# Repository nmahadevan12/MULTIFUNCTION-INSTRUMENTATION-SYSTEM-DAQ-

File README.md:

# Multifunction Instrumentation System (M.I.S.)

**Developed by Nikhil Mahadevan**

A portable, Raspberry Pi–powered electronic test bench that replaces six lab instruments — ohmmeter, voltmeter, DC reference, square/sine function generator, and frequency meter — with one integrated DAQ platform.

---

## Table of Contents

- [Overview](#overview)
- [Instrument Summary](#instrument-summary)
- [System Architecture](#system-architecture)
- [Software Architecture](#software-architecture)
- [Hardware Design](#hardware-design)
  - [Power Supply](#41--12-v-power-supply)
  - [Ohmmeter](#42-ohmmeter)
  - [Voltmeter](#43-voltmeter)
  - [DC Reference](#44-dc-reference)
  - [Square Wave Generator](#45-square-wave-generator)
  - [Sine Wave Measurement](#46-sine-wave-measurement-frequency-meter)
  - [Sine Wave Generator](#47-sine-wave-generator)
- [PCB Design](#pcb-design-kicad)
- [GPIO Pin Map](#gpio-pin-map-system)
- [Getting Started](#getting-started)
- [Demo Videos](#demo-videos)
- [Skills Demonstrated](#skills-demonstrated)

---

## Overview

The Multifunction Instrumentation System integrates oscilloscopes, function generators, and multimeters into a single-board computer platform using the **Raspberry Pi 4** as the central processing unit. Custom analog front-end circuits handle signal conditioning, comparison, and generation; Python firmware orchestrates measurement, waveform output, and a responsive menu-driven UI from a single application.

> [!TIP]
> **Documentation convention:** Images show only schematics, photos, and oscilloscope captures. All objectives, theory, and figure captions are written as markdown text below each image.

<details open>
<summary><strong>At a Glance</strong></summary>

| | |
|---|---|
| **Controller** | Raspberry Pi 4 (sole processor — no external MCU) |
| **Interface** | 20×4 I²C LCD + KY-040 rotary encoder with pushbutton |
| **Analog front-end** | TL084/TL081 op-amps, LM339 comparators, MCP4131/MCP4231 digipots |
| **Power** | 24 V DC input → ±12 V virtual-ground split-rail supply |
| **Firmware** | ~970 lines of Python — SAR measurement, hardware PWM, pigpio edge detection |
| **PCB** | 4-layer KiCad hierarchical design with Gerber manufacturing files |

</details>

<details>
<summary><strong>Project Objectives</strong></summary>

1. **Instrument design**
   - Ohmmeter (500 Ω – 10 kΩ)
   - Voltmeter (−5 V to +5 V)
   - DC reference (−5 V to +5 V)
   - Sine wave frequency measurement (1 – 10 kHz)
   - Function generator — square wave (100 Hz – 10 kHz, ±10 V) and sine wave (1 – 10 kHz, 0 – 10 V pk)

2. **System integration**
   - ±12 V power supply from 24 V input
   - Software-driven successive-approximation measurement (digipot + comparator)
   - Rotary-encoder UI on 20×4 LCD

3. **PCB layout**
   - Full KiCad schematic and 4-layer board design sized to the Raspberry Pi footprint

</details>

<details>
<summary><strong>Design Constraints</strong></summary>

| Category | Constraint |
|---|---|
| **Software** | All logic in Python; pigpio daemon for timing-critical PWM and edge detection |
| **Controller** | Raspberry Pi 4 only — no external microcontrollers |
| **Digipots** | Maximum of 4 digital potentiometers (MCP4131 ×3, MCP4231 ×1 dual-channel) |
| **Power** | All analog power derived from 24 V DC (LCD powered separately); Pi via USB-C |
| **Mechanical** | Pi Hat required — all GPIO routed through hat connector |

</details>

---

## Instrument Summary

| Instrument | Range | Accuracy | Update Rate |
|:---|:---|:---|:---|
| 🔵 **Ohmmeter** | 500 Ω – 10 kΩ | ±10% | 500 ms |
| 🟢 **Voltmeter** | −5 V to +5 V | ±0.2 V | 500 ms |
| 🟡 **DC Reference** | −5.00 V to +4.80 V (32 steps) | ±0.2 V | On demand |
| 🟠 **Square Wave** | 100 Hz – 10 kHz, ±10 V pk | ±1 V amplitude | Real-time PWM |
| 🟣 **Sine Wave** | 1 – 10 kHz, 0 – 10 V pk | ±0.2 V amplitude | Real-time audio |
| 🔴 **Frequency Meter** | 1 – 10 kHz | ±1% | 500 ms |

---

## System Architecture

```mermaid
flowchart LR
    subgraph UI["🖥️ User Interface"]
        LCD["20×4 I²C LCD"]
        ENC["Rotary Encoder"]
    end

    subgraph SW["🐍 Python Firmware"]
        MENU["Menu State Machine"]
        SAR["SAR Engine"]
        PWM["Hardware PWM"]
        FREQ["Edge Detection"]
    end

    subgraph HW["⚡ Analog Front-End"]
        PS["±12V Supply"]
        MEAS["Ohm / Volt"]
        GEN["Wave Gen"]
        DCREF["DC Ref"]
    end

    ENC --> MENU --> LCD
    MENU --> SAR & PWM & FREQ
    SAR & PWM & FREQ --> HW
    PS --> HW
```

---

## Software Architecture

Software is the core of the system — it links the user interface to hardware modules, converts raw comparator signals into resistance/voltage values, controls waveform timing, and keeps the LCD updated.

<details open>
<summary><strong>Platform & Libraries</strong></summary>

| Layer | Technology |
|---|---|
| OS | Raspberry Pi OS |
| Execution | Standalone Python script (`Main Code/16.py`) |
| GPIO / PWM | `RPi.GPIO`, `pigpio` (hardware PWM + µs edge timestamps) |
| SPI | `spidev` — MCP4131 / MCP4231 digital potentiometers |
| I²C | `smbus2`, `RPLCD` — 20×4 character LCD |
| UI input | `gpiozero` — rotary encoder + button callbacks |

</details>

<details>
<summary><strong>Navigation & Main Loop</strong></summary>

The interface is a **stack-based menu tree** with automatic hardware cleanup on back-navigation. Measurement modes sample every **500 ms**; the LCD refreshes on a 50 ms display flag with thread-safe writes.

To ensure a highly responsive user interface, the **500 ms** hardware measurement routines run asynchronously or utilize non-blocking sleep intervals. This prevents the synchronous 8-bit SPI SAR sweeps from blocking encoder interrupt callbacks or delaying the **50 ms** LCD UI refresh cycle.

```
while True:
    if display_needs_update → render_interface()
    if measurement_mode     → sample hardware every 500 ms
    if leaving_mode         → cleanup GPIO / stop waveforms
    sleep(0.05)
```

</details>

<details>
<summary><strong>Per-Instrument Firmware</strong></summary>

| Instrument | Key Implementation |
|---|---|
| **Square wave** | Hardware PWM GPIO 12 + MCP4231 amplitude/offset over SPI |
| **Sine wave** | Pi audio jack + `speaker-test`; MCP4131 amplitude (CS GPIO 17) |
| **Ohmmeter** | 8-iter SAR on MCP4131; `R = R_known × (step / (128 − step))` |
| **Voltmeter** | SAR on GPIO 6; lookup table + linear interpolation |
| **DC Reference** | 5-bit R-2R on GPIO 14, 15, 18, 23, 24 |
| **Frequency** | pigpio edge callbacks GPIO 25; 100-period buffer, >2σ outlier reject |

</details>

> [!IMPORTANT]
> All waveform and DC outputs **automatically disable** when leaving a menu — a built-in safety interlock.

---

## Hardware Design

### 4.1 ±12 V Power Supply

*Figure 4.1.1: Power Supply Schematic*

<details open>
<summary><strong>Power Supply — Theory & Integration</strong></summary>

**Objective:** Split a +24 V DC input into symmetric +12 V and −12 V rails to power op-amps throughout the system. Rails must remain stable under varying load.

**Theory of Operation:** Virtual ground from a 24 V source. TL081 unity-gain follower at the 12 V midpoint drives IRFZ34N + IRF5305 push-pull stage. Virtual ground tied to Pi GND → +12 V above, −12 V below. The virtual ground node acts as the absolute **0 V** reference point for all analog measurements. To prevent heavy analog return currents from injecting noise into the digital plane, the Raspberry Pi GND is tied to this virtual ground at a **single star-ground point** right at the power entry terminal.

1. **Voltage reference:** Matched 10 kΩ divider + Zener clamping → 12 V at TL081 pin 3
2. **Unity-gain buffering:** 100 kΩ feedback drives MOSFET gates
3. **Push-pull output:** NMOS sources / PMOS sinks load current at virtual ground
4. **Output stabilization:** 220 µF bulk caps per rail

**Physical Integration:** Breadboard; ±12 V via terminal blocks. **GPIO:** None — analog only.

</details>

<details>
<summary><strong>Power Supply — Test Results</strong></summary>

| Test Condition | Negative Rail | Positive Rail | Current |
|---|---|---|---|
| Both loads connected | −12.04 V | +12.05 V | ~12 mA each |
| No load | −12.05 V | +12.06 V | — |
| Negative load only | 12.05 V | — | 12.10 mA |
| Positive load only | — | 12.06 V | 12.08 mA |

</details>

> [!WARNING]
> MOSFETs run warm under heavy load. Observe electrolytic capacitor polarity on each rail.

---

### 4.2 Ohmmeter

*Figure 4.2.1: Ohmmeter Schematic*

<details open>
<summary><strong>Ohmmeter — Theory & GPIO</strong></summary>

**Objective:** High-accuracy auto-ranging digital ohmmeter for **500 Ω to 10 kΩ**.

**Theory of Operation:** Voltage divider with unknown resistor vs. **7-bit MCP4131** programmable reference. Successive approximation across 128 wiper steps; LM339 comparator on GPIO 21. LCD updates every 500 ms with ±10% tolerance. A fixed series current-limiting resistor (**R_limit = 1 kΩ**) is placed in series with the unknown device under test (DUT). This keeps the maximum current through the MCP4131 wiper well below its absolute maximum rating of **2.5 mA** even when measuring low resistances down to **500 Ω**.

| Signal | GPIO | Component Pin |
|---|---|---|
| Chip Select (CS) | 8 | MCP4131 Pin 1 |
| SPI Clock (SCK) | 11 | MCP4131 Pin 2 |
| SPI Data (SDI/SDO) | 10 | MCP4131 Pin 3 |
| Comparator Output | 21 | LM339 Output |

> [!NOTE]
> **SAR performance (8-bit search):** Each iteration writes one MCP4131 wiper step over SPI (1 MHz, 2-byte frame ≈ 16 µs), waits **5 ms** for the divider/comparator to settle (`sleep(0.005)`), then reads GPIO 21. Eight bisection steps → **≈40 ms** per resistance reading, well under the **500 ms** LCD refresh cadence. Quantization is set by the **128-step** digipot (7-bit effective range); resistance resolution is non-linear with step (`R = R_known × step / (128 − step)`) and tightest near the matched mid-scale point. Because the voltage-divider topology yields a non-linear resolution across the 128-step digipot, measurement precision peaks when the unknown resistance closely matches the internal reference (**R_known**). Near the outer bounds (**500 Ω** and **10 kΩ**), step-size quantization broadens, which accounts for the specified worst-case **±10%** tolerance.

</details>

---

### 4.3 Voltmeter

*Figure 4.3.1: Voltmeter Schematic*

<details open>
<summary><strong>Voltmeter — Theory & GPIO</strong></summary>

**Objective:** Measure **−5 V to +5 V** at ±0.2 V accuracy. Dual-source: external input or internal DC reference verification.

**Theory of Operation:**

1. **U2 — Inverting summing amp:** Maps −5 V to +5 V → 0 V to −10 V
2. **U1 — Inverting amp:** Gain −1/3 → **0 to +3.3 V**
3. **U3 — MCP4131:** 128-step programmable reference via SPI
4. **U5A — LM339:** Comparator with 10 kΩ pull-up
5. **GPIO 6:** Binary search until reference matches test voltage

| Signal | GPIO | Component Pin |
|---|---|---|
| Chip Select (CS) | 8 | MCP4131 Pin 1 |
| SPI Clock (SCK) | 11 | MCP4131 Pin 2 |
| SPI Data (SDI/SDO) | 10 | MCP4131 Pin 3 |
| Comparator Output | 6 | LM339 Pin 13 |

> [!NOTE]
> **SAR performance (8-bit search):** Same 8-iteration binary search as the ohmmeter — one SPI wiper write + **5 ms** settle per step → **≈40 ms** total sweep, safely below the **500 ms** display refresh rate. The ±10 V input span maps to 128 comparator steps, giving a theoretical **≈78 mV/step** (`10 V / 128 ≈ 78 mV`); linear interpolation between calibrated lookup points improves display accuracy to ±0.2 V.

**Calibration & Testing:** Verified against reference multimeter across full range. SAR converges in 8 iterations. ±0.2 V accuracy; best precision near 0 V.

</details>

---

### 4.4 DC Reference

*Figure 4.4.1: DC Ref Schematic*

<details open>
<summary><strong>DC Reference — Theory</strong></summary>

**Objective:** Programmable DC output **−5 V to +5 V** in 0.625 V steps (32 levels).

1. **R-2R DAC:** GPIO 14, 15, 18, 23, 24 → binary-weighted divider
2. **U2 — Non-inverting amp:** Gain ≈ 3.03 scales 0–3.3 V → 0–10 V
3. **U3 — Difference amp:** +5 V bias → **−5 V to +5 V** output

**Calibration & Testing:** Output verified across all 32 steps with a reference multimeter. Monotonic response confirmed from −5 V to +5 V.

</details>

<details>
<summary><strong>Previous Design Iteration (Figure 4.4.2)</strong></summary>

*Figure 4.4.2: Previous DC Ref Schematic*

Original binary-weighted DAC with per-GPIO comparator buffers suffered **cross-loading**. R-2R ladder maintains uniform 2R impedance regardless of bit pattern. The R-2R ladder ensures the digital pins always see a constant output impedance of **R** (or **2R** depending on the node), preventing the voltage sag and non-monotonicity caused by varying pin source impedances in the previous binary-weighted layout.

</details>

---

### 4.5 Square Wave Generator

*Figure 4.5.1: Square Wave Schematic*

<details open>
<summary><strong>Square Wave — Theory & GPIO</strong></summary>

**Objective:** Variable square wave centered at **0 V**, up to **±10 V**, high-Z output for oscilloscope use.

**Theory:** Pi hardware PWM GPIO 12 → MCP4231 amplitude + offset → difference amplifier (gain 10) → ±10 V. The hardware PWM output from GPIO 12 passes through a dedicated **RC low-pass filter** stage to smooth high-frequency switching transients and stabilize the signal envelope before amplitude scaling, maintaining waveform integrity across the **100 Hz to 10 kHz** band.

| Signal | GPIO | MCP4231 Pin |
|---|---|---|
| PWM Output | 12 | Ch1 Pin B |
| Chip Select | 7 | Pin 1 |
| SPI Clock | 11 | Pin 3 |
| SPI Data In | 10 | Pin 4 |

**Calibration & Testing:**

- **Figure 4.5.2 — ±7 V initial:** −7.24 V min / +5.95 V max (miscentered)
- **Figure 4.5.3 — ±5 V @ 100 Hz:** Offset ratio **0.45** → ±3% centering
- **Figure 4.5.4 — ±10 V @ 100 Hz:** Full swing confirmed

</details>

<details>
<summary><strong>Oscilloscope Captures</strong></summary>

</details>

---

### 4.6 Sine Wave Measurement (Frequency Meter)

*Figure 4.6.1: Sine Wave Measurement Schematic*

<details open>
<summary><strong>Frequency Meter — Theory & GPIO</strong></summary>

**Objective:** Measure **0 V to +10 V** sine input frequency from **1 kHz to 10 kHz**.

**Theory:** LM339 threshold at **+1.65 V** → digital edges on GPIO 25 → **f = 1/T**. 100-period rolling buffer with >2σ outlier rejection.

**pigpio edge architecture:** On standard Linux (non-real-time), Python thread scheduling would jitter any bit-banged timing. The `pigpio` daemon sidesteps this by sampling GPIO transitions with **hardware-level DMA**, stamping each rising edge with a **microsecond-accurate tick** (`pigpio.tickDiff`) in a background buffer. The Python callback only appends period samples; `compute_frequency()` runs on the 500 ms UI loop, decoupling the timing-critical edge capture from GIL contention and kernel scheduling delay.

| Signal | GPIO | Component Pin |
|---|---|---|
| Comparator Output | 25 | LM339 Output |
| External Input | — | LM339 Non-Inverting Input |
| Reference (+1.65 V) | — | LM339 Inverting Input |

**Calibration & Testing:** ±2% tolerance across 1 – 10 kHz.

</details>

---

### 4.7 Sine Wave Generator

<details open>
<summary><strong>Sine Wave Generator — Theory & GPIO</strong></summary>

**Objective:** **0 – 10 V peak** sine wave from **1 kHz to 10 kHz**.

1. **U3 — TL081 buffer:** Pi audio jack + −5 V DC offset
2. **U4 & U5 — Scaling:** Normalize to 0–3.3 V. Because the Raspberry Pi audio jack outputs a line-level AC signal (≈1 V pk-pk), **U4** is configured as a non-inverting amplifier with a hardware gain of **A_v ≈ 3.3** to scale the raw audio voltage up to the required **3.3 V** internal logic dynamic range before attenuation.
3. **U10 — MCP4131:** Digital attenuation via SPI
4. **U11 & U12 — Output:** Reconstruct to 0–10 V

| Signal | GPIO | MCP4131 Pin |
|---|---|---|
| Chip Select | 17 | Pin 1 |
| SPI Clock | 11 | Pin 2 |
| SPI Data | 10 | Pin 3 |

</details>

---

## PCB Design (KiCad)

*Figure 5.2.1: Final PCB Schematic*

*Figure 5.2.2: Final PCB Board*

<details>
<summary><strong>PCB Design Details</strong></summary>

- **CAD tool:** KiCad — free, full-featured
- **Schematic:** Hierarchical sub-sheets per instrument; max 4 layers
- **Layout:** Subsystem grouping, through-hole + SMD passives, 45° routing
- **Manufacturing:** DRC-checked Gerbers in `PCBDesign/` (designed, not manufactured)

</details>

---

## GPIO Pin Map (System)

<details open>
<summary><strong>Full GPIO Map — click to expand</strong></summary>

| GPIO | Signal | Component | Description |
|:---:|:---|:---|:---|
| 2, 3 | SDA, SCL | LCD | I²C character display |
| 6 | Input | LM339 | Voltmeter comparator |
| 7 | SPI CS | MCP4231 | Square wave digipot |
| 8 | SPI CS | MCP4131 | Ohmmeter / voltmeter digipot |
| 10 | SPI MOSI | MCP4131/4231 | SPI data |
| 11 | SPI SCLK | MCP4131/4231 | SPI clock |
| 12 | HW PWM | — | Square wave output |
| 13, 19 | Input | KY-040 | Rotary encoder A/B |
| 14, 15, 18, 23, 24 | Output | R-2R ladder | DC reference (5-bit) |
| 17 | SPI CS | MCP4131 | Sine amplitude digipot |
| 21 | Input | LM339 | Ohmmeter comparator |
| 25 | Interrupt | LM339 | Frequency measurement |
| 26 | Input | KY-040 | Encoder button (3 s hold = back) |

</details>

---

## Getting Started

> [!NOTE]
> GPIO access requires `sudo`. The `pigpio` daemon must be running for PWM and frequency measurement.

<details open>
<summary><strong>Install & Run</strong></summary>

```bash
sudo apt update && sudo apt install -y python3-pip pigpio python3-pigpio alsa-utils
sudo systemctl enable --now pigpio
pip install -r requirements.txt
sudo python3 "Main Code/16.py"
```

</details>

<details>
<summary><strong>Controls Cheat Sheet</strong></summary>

| Action | Control |
|---|---|
| Scroll | Rotate encoder |
| Select / confirm | Short press |
| Back / cancel | Hold 3 seconds |
| Edit value | Rotate in edit mode, press to confirm |

Power Pi via **USB-C**, analog circuits via **24 V DC**. Wait ~20 s after boot.

</details>

---

## Demo Videos

<details open>
<summary><strong>Watch demos — click any link</strong></summary>

| Feature | Link |
|---|---|
| Power-on & setup | [YouTube](https://youtu.be/CEZYySeiEv4) |
| Menu navigation | [YouTube](https://youtu.be/Nd_8IkFf7bE) |
| Ohmmeter | [YouTube](https://youtu.be/j0UAiwsbkE0) |
| Voltmeter (external) | [YouTube](https://youtube.com/shorts/AqCL2ivuH78) |
| Voltmeter (internal ref) | [YouTube](https://youtube.com/shorts/lTq6MlFrF2s) |
| Square wave | [YouTube](https://youtube.com/shorts/NfCk3m-b2u8) |
| Sine wave | [YouTube](https://youtube.com/shorts/mf1v4rBYL3M) |
| Frequency measurement | [YouTube](https://youtube.com/shorts/Z5qWBG-sBkY) |

</details>

---

## Future Improvements

> [!TIP]
> Planned next steps: 12–16 bit external ADC, manufactured 4-layer PCB with ground planes, BNC/screw-terminal I/O, on-board regulators, active analog shielding.

---

## Skills Demonstrated

<table>
<tr>
<td width="50%">

**Embedded Systems**
- GPIO, hardware PWM, SPI/I²C
- pigpio edge detection
- SAR algorithms
- Thread-safe concurrent access

**Software Engineering**
- State-machine UI
- Stack navigation
- Lookup tables
- ~970 LOC firmware

</td>
<td width="50%">

**Analog Design**
- Op-amp conditioning
- Comparator front-ends
- R-2R DAC
- Virtual-ground power

**PCB / Systems**
- KiCad hierarchical design
- 4-layer layout
- End-to-end HW/SW co-design
- Safety interlocks

</td>
</tr>
</table>

---

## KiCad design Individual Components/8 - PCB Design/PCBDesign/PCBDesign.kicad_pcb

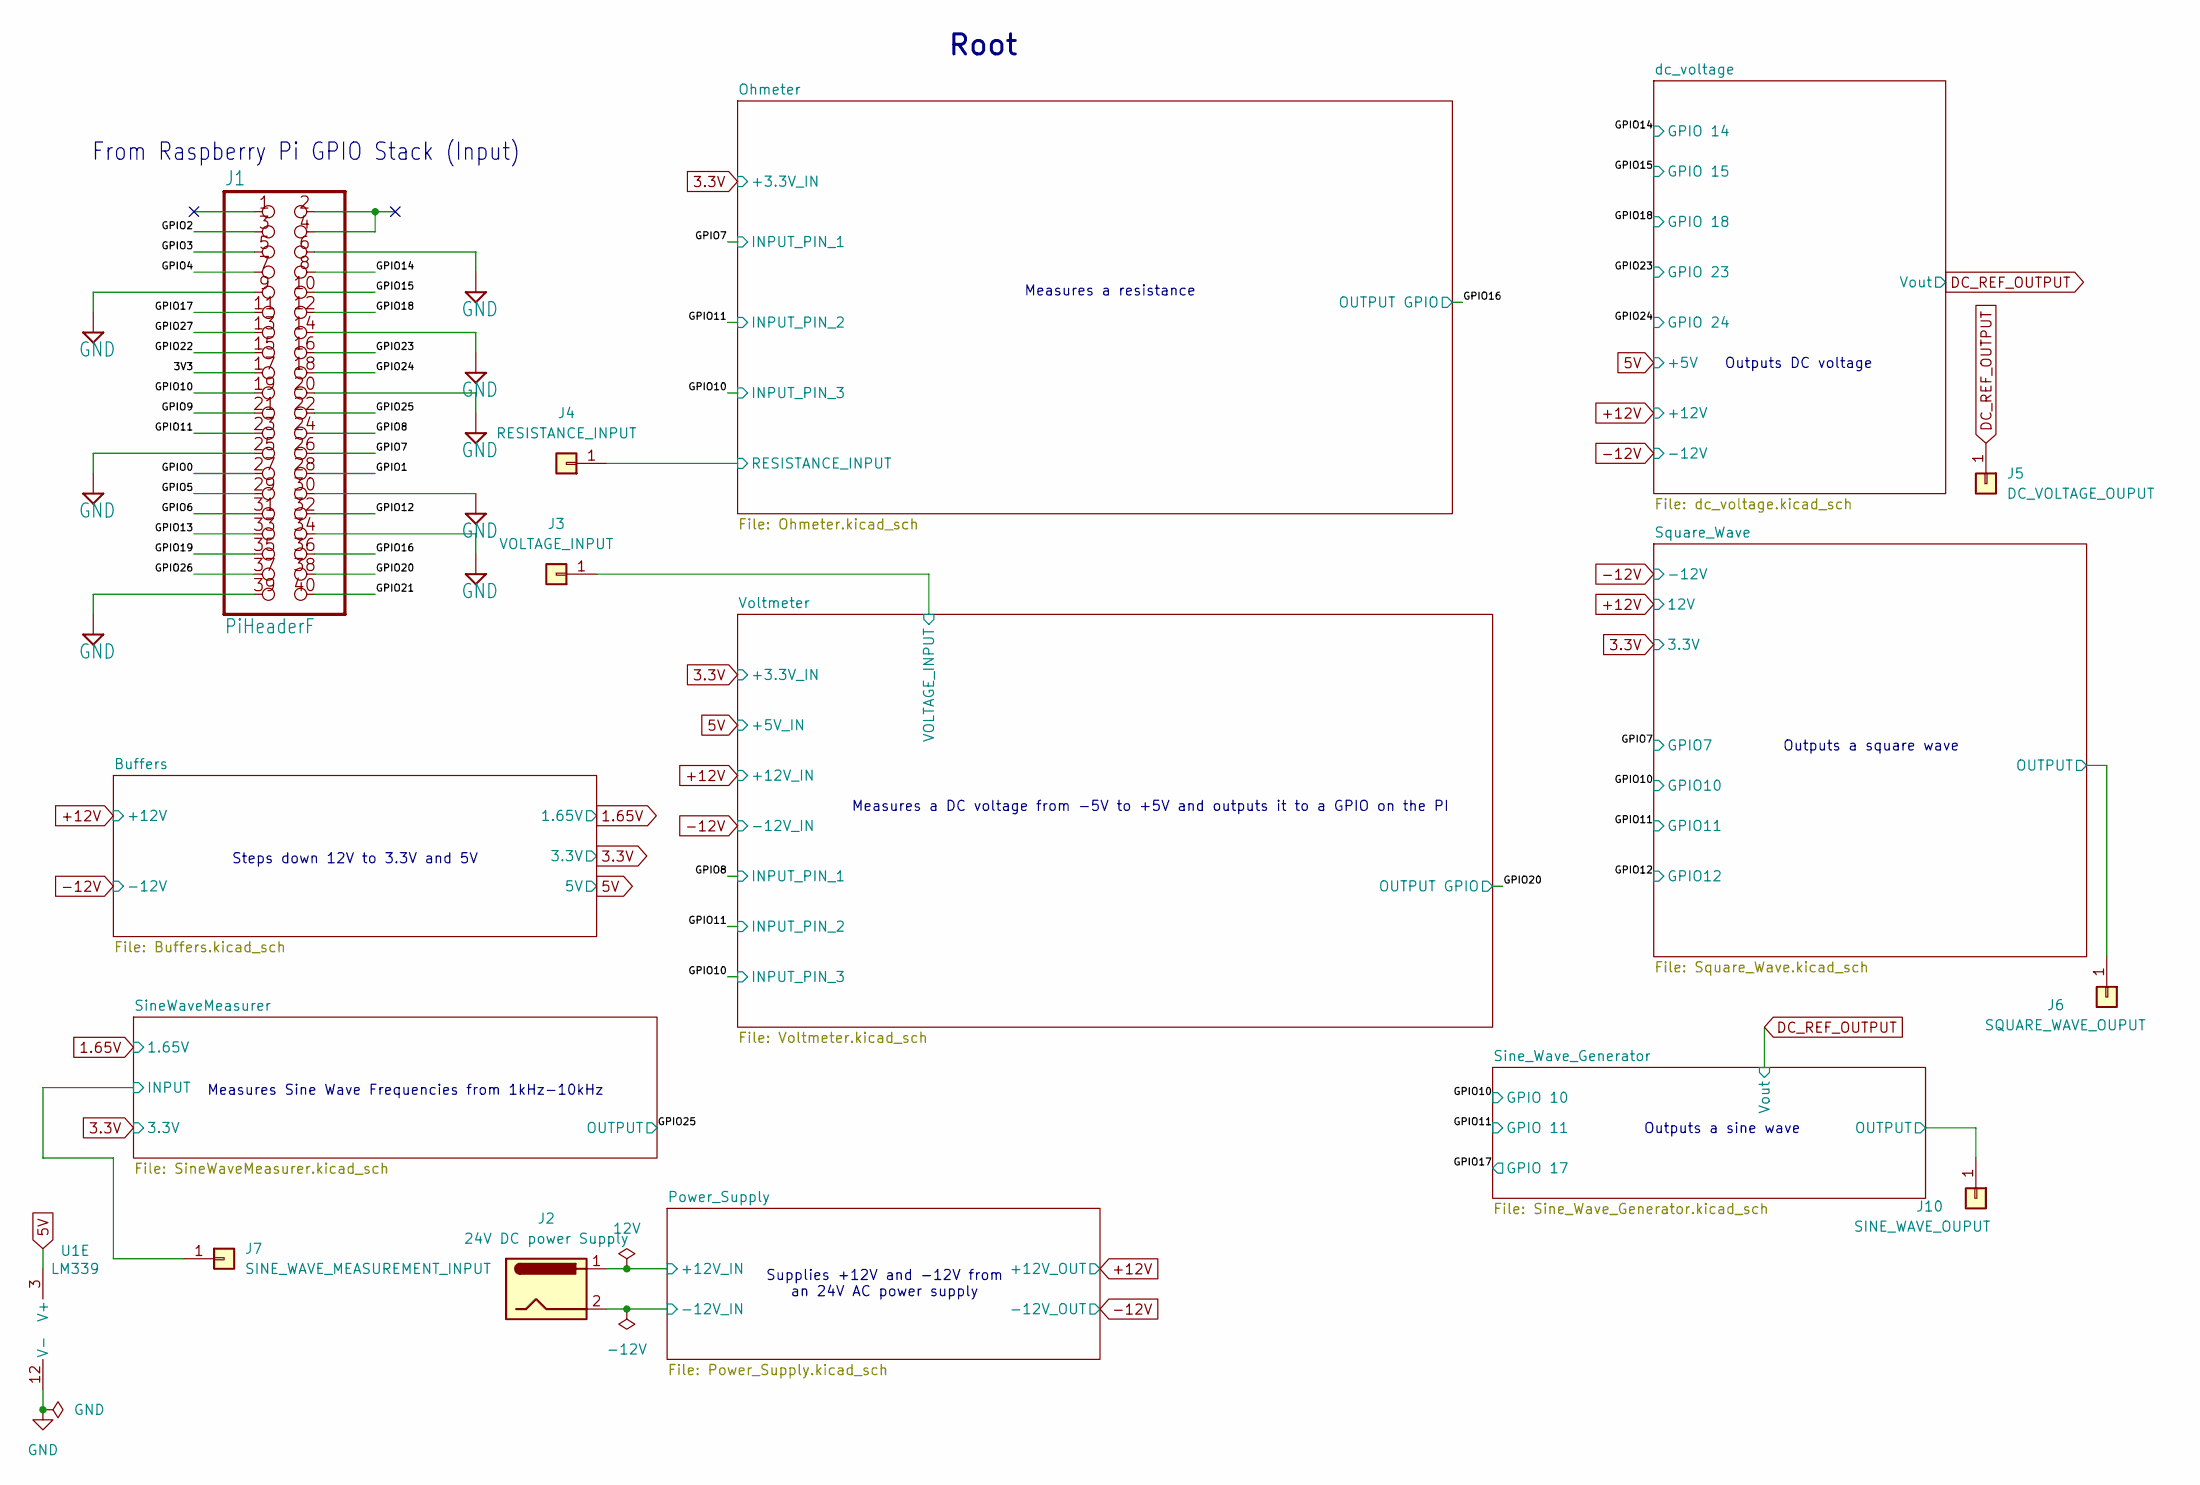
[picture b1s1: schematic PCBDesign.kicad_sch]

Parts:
J1: PiHeaderF; PinSocket_2x20_P2.54mm_Vertical
J2: 24V DC power Supply; BarrelJack_Horizontal
J3: VOLTAGE_INPUT; PinHeader_1x01_P1.00mm_Vertical
J4: RESISTANCE_INPUT; PinHeader_1x01_P1.00mm_Vertical
J5: DC_VOLTAGE_OUPUT; PinHeader_1x01_P1.00mm_Vertical
J6: SQUARE_WAVE_OUPUT; PinHeader_1x01_P1.00mm_Vertical
J7: SINE_WAVE_MEASUREMENT_INPUT; PinHeader_1x01_P1.00mm_Vertical
J10: SINE_WAVE_OUPUT; PinHeader_1x01_P1.00mm_Vertical
U1: LM339; DIP-14_W7.62mm

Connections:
3.3V: J4.1 (Pin_1_1); also elsewhere on the board
5V: U1.3 (V+); also elsewhere on the board
+12V: J2.1; also elsewhere on the board
-12V: J2.2; also elsewhere on the board
/3V3: J1.17
/GPIO0: J1.27
/GPIO1: J1.28
/GPIO2: J1.3
/GPIO3: J1.5
/GPIO4: J1.7
/GPIO5: J1.29
/GPIO6: J1.31
/GPIO7: J1.26; also elsewhere on the board
/GPIO8: J1.24; also elsewhere on the board
/GPIO9: J1.21
/GPIO10: J1.19; also elsewhere on the board
/GPIO11: J1.23; also elsewhere on the board
/GPIO12: J1.32; also elsewhere on the board
/GPIO13: J1.33
/GPIO14: J1.8; also elsewhere on the board
/GPIO15: J1.10; also elsewhere on the board
/GPIO16: J1.36; also elsewhere on the board
/GPIO17: J1.11; also elsewhere on the board
/GPIO18: J1.12; also elsewhere on the board
/GPIO19: J1.35
/GPIO20: J1.38; also elsewhere on the board
/GPIO21: J1.40
/GPIO22: J1.15
/GPIO23: J1.16; also elsewhere on the board
/GPIO24: J1.18; also elsewhere on the board
/GPIO25: J1.22; also elsewhere on the board
/GPIO26: J1.37
/GPIO27: J1.13
/SineWaveMeasurer/INPUT: J7.1 (Pin_1_1); also elsewhere on the board
/Square_Wave/OUTPUT: J6.1 (Pin_1_1); also elsewhere on the board
/Voltmeter/VOLTAGE_INPUT: J3.1 (Pin_1_1); also elsewhere on the board
DC_REF_OUTPUT: J5.1 (Pin_1_1), J10.1 (Pin_1_1); also elsewhere on the board
GND: J1.6, J1.9, J1.14, J1.20, J1.25, J1.30, J1.34, J1.39, U1.12 (V-); also elsewhere on the board

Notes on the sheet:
Measures a DC voltage from -5V to +5V and outputs it to a GPIO on the PI
Measures Sine Wave Frequencies from 1kHz-10kHz
Supplies +12V and -12V from an 24V AC power supply
Outputs a sine wave
From Raspberry Pi GPIO Stack (Input)
Outputs a square wave
Outputs DC voltage
Steps down 12V to 3.3V and 5V
Measures a resistance
Root

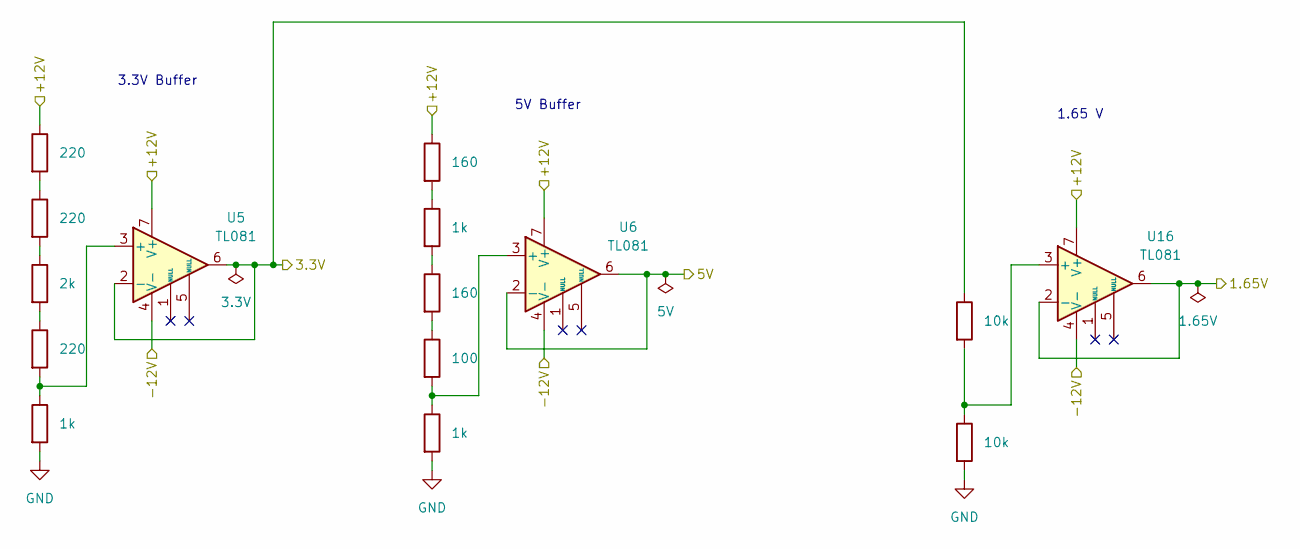
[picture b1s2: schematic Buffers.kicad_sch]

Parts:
R7, R8, R10: 220; R_0603_1608Metric
R9: 2k; R_0603_1608Metric
R11, R13, R16: 1k; R_0603_1608Metric
R12, R14: 160; R_0603_1608Metric
R15: 100; R_0603_1608Metric
R42, R46: 10k; R_0603_1608Metric
U5, U6, U16: TL081; DIP-8_W7.62mm

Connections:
1.65V: U16.2 (-), U16.6
3.3V: R46.1, U5.2 (-), U5.6; also elsewhere on the board
5V: U6.2 (-), U6.6; also elsewhere on the board
+12V: R7.1, R12.1, U5.7 (V+), U6.7 (V+), U16.7 (V+); also elsewhere on the board
-12V: U5.4 (V-), U6.4 (V-), U16.4 (V-); also elsewhere on the board
GND: R11.2, R16.2, R42.2; also elsewhere on the board
unnamed: R7.2, R8.1
unnamed: R8.2, R9.1
unnamed: R9.2, R10.1
unnamed: R12.2, R13.1
unnamed: R13.2, R14.1
unnamed: R14.2, R15.1
unnamed: R10.2, R11.1, U5.3 (+)
unnamed: R15.2, R16.1, U6.3 (+)
unnamed: R42.1, R46.2, U16.3 (+)

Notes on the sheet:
3.3V Buffer
5V Buffer
1.65 V

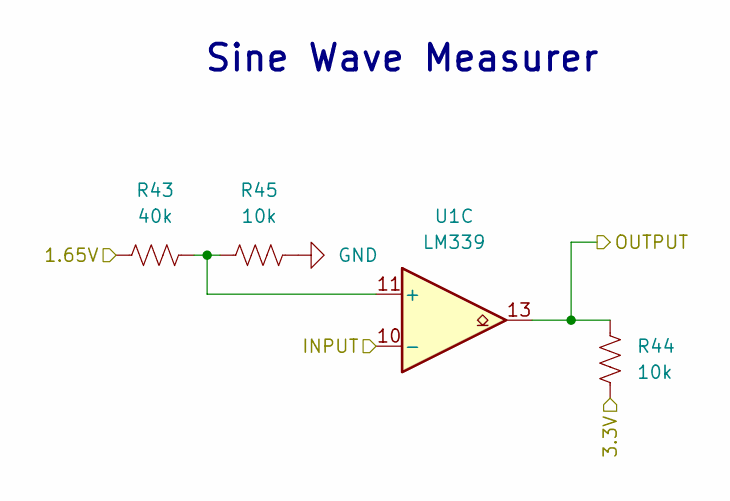
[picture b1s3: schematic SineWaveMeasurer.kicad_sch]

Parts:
R43: 40k
R44, R45: 10k
U1: LM339; DIP-14_W7.62mm

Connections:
/GPIO25: R44.1, U1.13; also elsewhere on the board
/SineWaveMeasurer/INPUT: U1.10 (-); also elsewhere on the board
unnamed: R43.2, R45.1, U1.11 (+)

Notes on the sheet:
Sine Wave Measurer

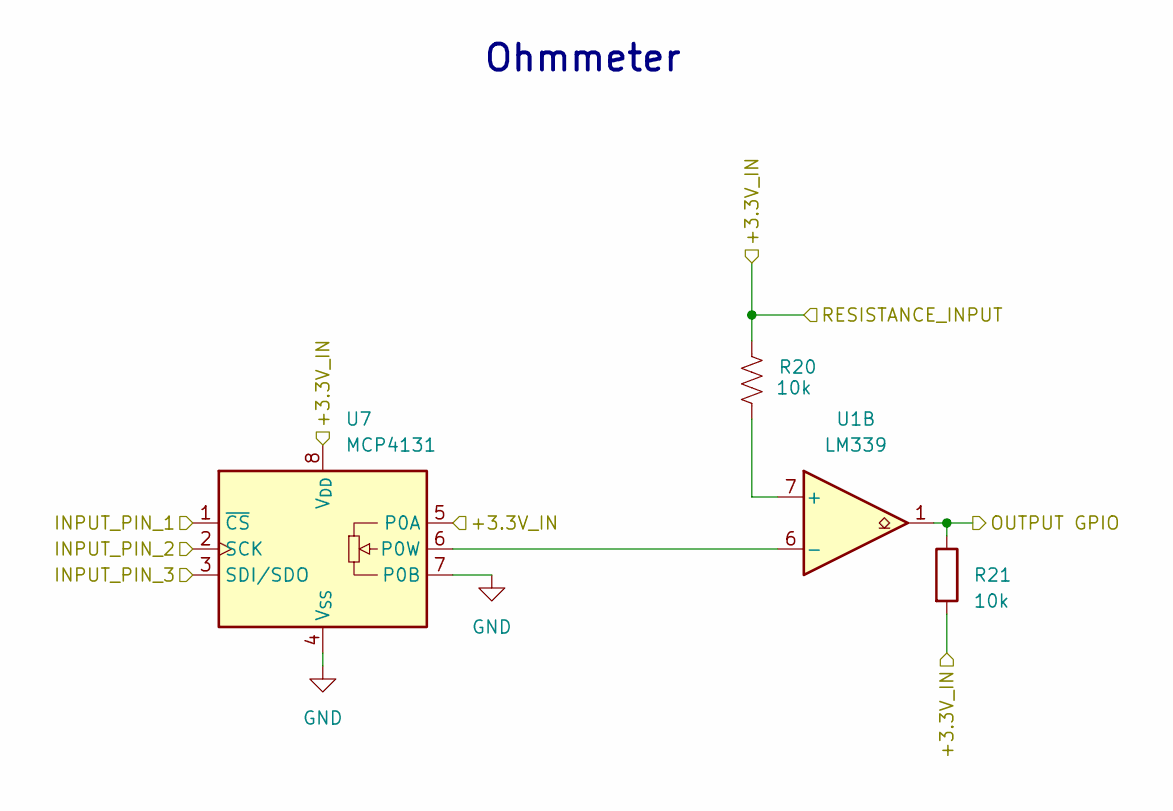
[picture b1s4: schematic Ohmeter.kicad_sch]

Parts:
R20, R21: 10k; R_0603_1608Metric
U1: LM339; DIP-14_W7.62mm
U7: MCP4131; DIP-8_W7.62mm

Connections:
3.3V: R20.1, R21.2, U7.5 (P0A), U7.8 (V_{DD}); also elsewhere on the board
/GPIO7: U7.1 (~CS); also elsewhere on the board
/GPIO10: U7.3 (SDI/SDO); also elsewhere on the board
/GPIO11: U7.2 (SCK); also elsewhere on the board
/GPIO16: R21.1, U1.1; also elsewhere on the board
GND: U7.4 (V_{SS}), U7.7 (P0B); also elsewhere on the board
unnamed: R20.2, U1.7 (+)
unnamed: U1.6 (-), U7.6 (P0W)

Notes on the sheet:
Ohmmeter

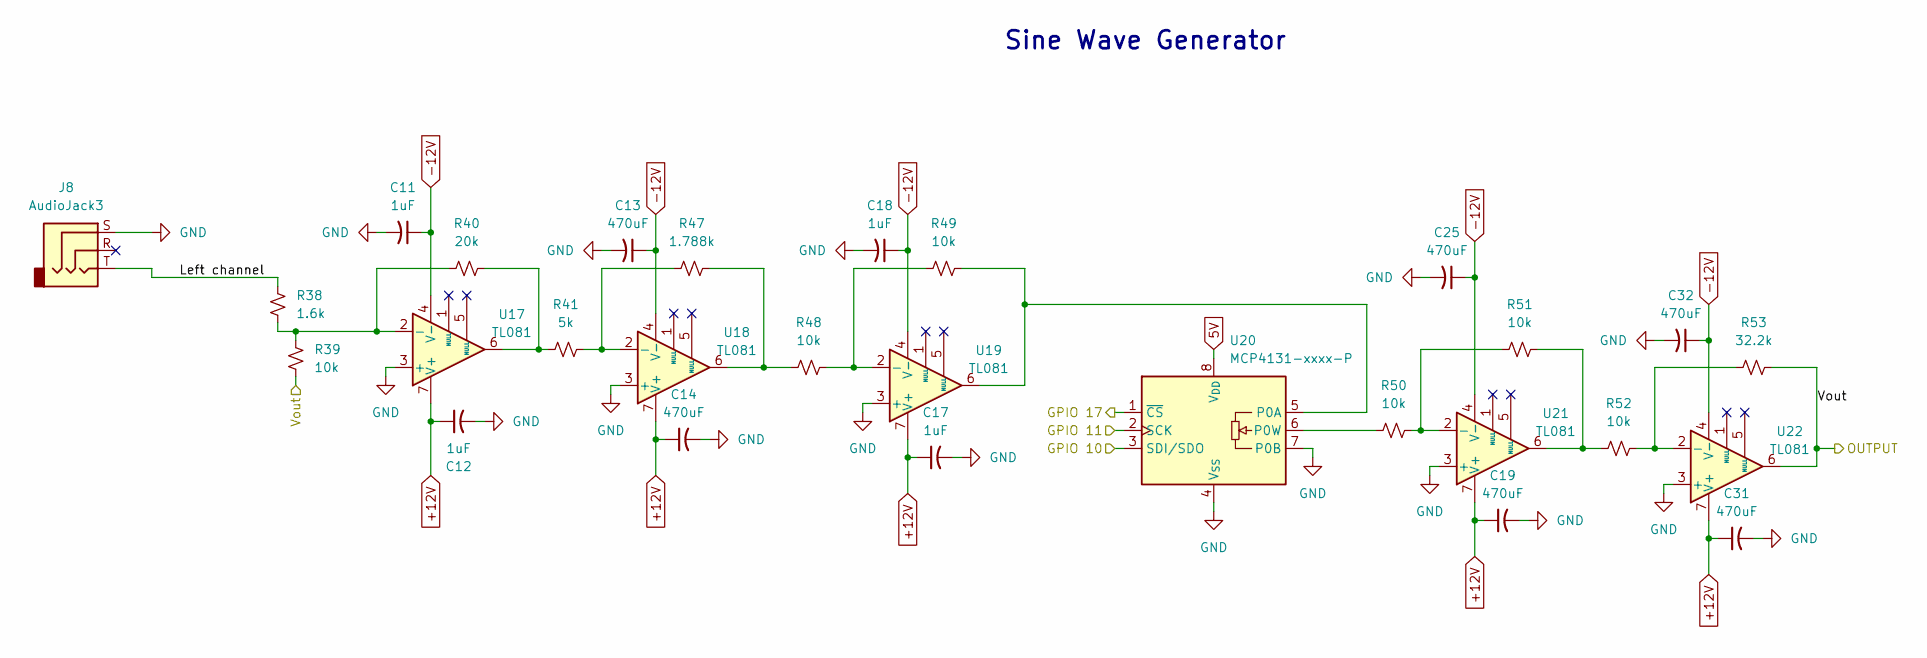
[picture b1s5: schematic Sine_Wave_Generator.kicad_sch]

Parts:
C11, C12, C17, C18: 1uF; CP_Elec_4x3
C13, C14, C19, C25, C31, C32: 470uF; CP_Elec_4x3
J8: AudioJack3; Jack_3.5mm_CUI_SJ1-3533NG_Horizontal
R38: 1.6k; R_0603_1608Metric
R39, R48, R49, R50, R51, R52: 10k; R_0603_1608Metric
R40: 20k; R_0603_1608Metric
R41: 5k; R_0603_1608Metric
R47: 1.788k; R_0603_1608Metric
R53: 32.2k; R_0603_1608Metric
U17, U18, U19, U21, U22: TL081; DIP-8_W7.62mm
U20: MCP4131-xxxx-P; DIP-8_W7.62mm

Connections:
5V: U20.8 (V_{DD}); also elsewhere on the board
+12V: C12.1, C14.1, C17.1, C19.1, C31.1, U17.7 (V+), U18.7 (V+), U19.7 (V+), U21.7 (V+), U22.7 (V+); also elsewhere on the board
-12V: C11.1, C13.1, C18.1, C25.1, C32.1, U17.4 (V-), U18.4 (V-), U19.4 (V-), U21.4 (V-), U22.4 (V-); also elsewhere on the board
/GPIO10: U20.3 (SDI/SDO); also elsewhere on the board
/GPIO11: U20.2 (SCK); also elsewhere on the board
/GPIO17: U20.1 (~CS); also elsewhere on the board
/Sine_Wave_Generator/Left channel: J8.T, R38.1
DC_REF_OUTPUT: R39.2, R53.2, U22.6; also elsewhere on the board
GND: C11.2, C12.2, C13.2, C14.2, C17.2, C18.2, C19.2, C25.2, C31.2, C32.2, J8.S, U17.3 (+), U18.3 (+), U19.3 (+), U20.4 (V_{SS}), U20.7 (P0B), U21.3 (+), U22.3 (+); also elsewhere on the board
unnamed: R40.2, R41.1, U17.6
unnamed: R47.2, R48.1, U18.6
unnamed: R51.2, R52.1, U21.6
unnamed: R38.2, R39.1, R40.1, U17.2 (-)
unnamed: R41.2, R47.1, U18.2 (-)
unnamed: R48.2, R49.1, U19.2 (-)
unnamed: R49.2, U19.6, U20.5 (P0A)
unnamed: R50.1, U20.6 (P0W)
unnamed: R50.2, R51.1, U21.2 (-)
unnamed: R52.2, R53.1, U22.2 (-)

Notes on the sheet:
Sine Wave Generator

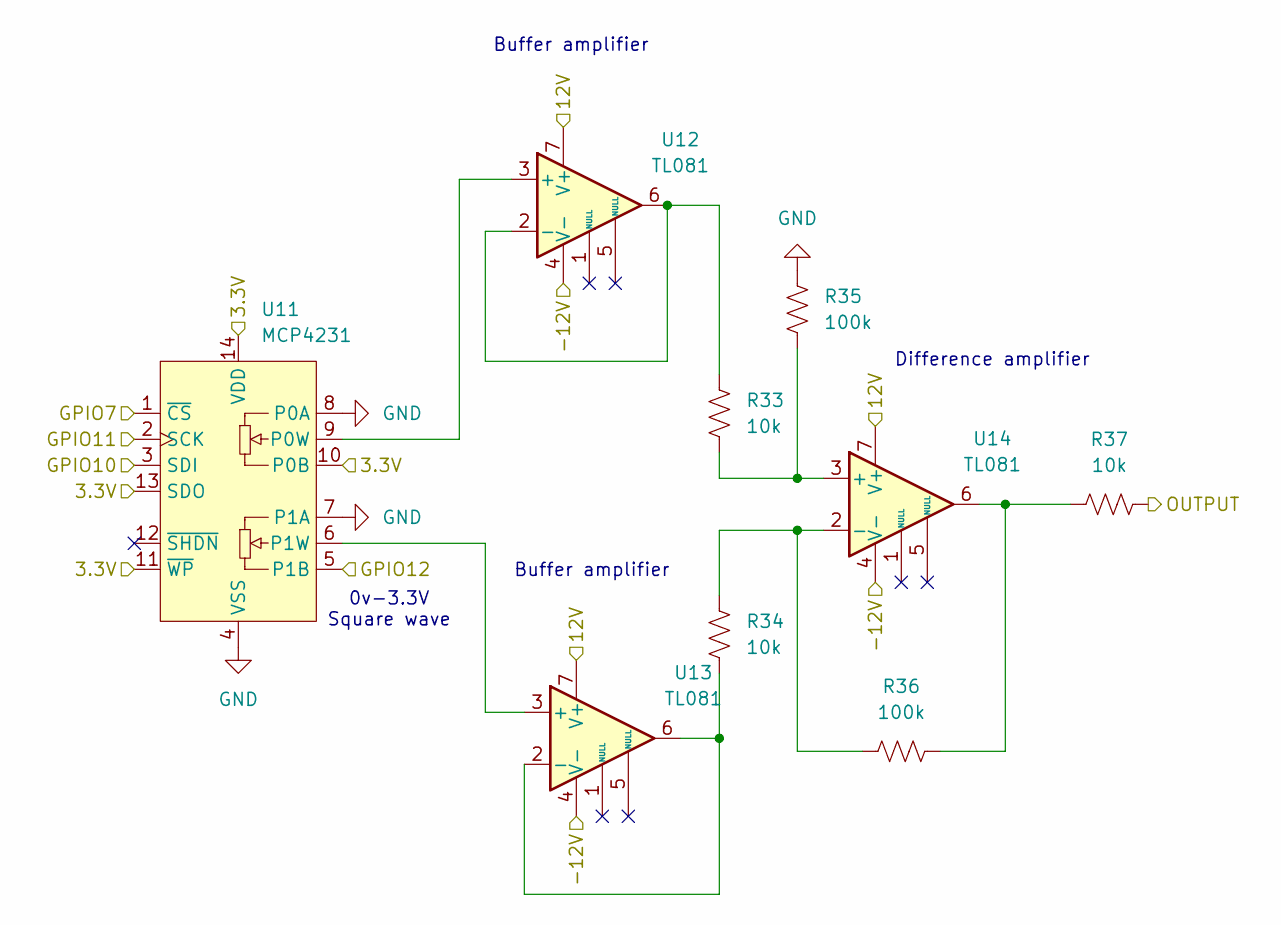
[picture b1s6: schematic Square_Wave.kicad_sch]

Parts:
R33, R34, R37: 10k; R_0603_1608Metric
R35, R36: 100k; R_0603_1608Metric
U11: MCP4231; DIP-14_W7.62mm
U12, U13, U14: TL081; DIP-8_W7.62mm

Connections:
3.3V: U11.10 (P0B), U11.11 (~WP), U11.13 (SDO), U11.14 (VDD); also elsewhere on the board
+12V: U12.7 (V+), U13.7 (V+), U14.7 (V+); also elsewhere on the board
-12V: U12.4 (V-), U13.4 (V-), U14.4 (V-); also elsewhere on the board
/GPIO7: U11.1 (~CS); also elsewhere on the board
/GPIO10: U11.3 (SDI); also elsewhere on the board
/GPIO11: U11.2 (SCK); also elsewhere on the board
/GPIO12: U11.5 (P1B); also elsewhere on the board
/Square_Wave/OUTPUT: R37.2; also elsewhere on the board
GND: R35.1, U11.4 (VSS), U11.7 (P1A), U11.8 (P0A); also elsewhere on the board
unnamed: R36.2, R37.1, U14.6
unnamed: U11.9 (P0W), U12.3 (+)
unnamed: U11.6 (P1W), U13.3 (+)
unnamed: R33.1, U12.2 (-), U12.6
unnamed: R34.2, U13.2 (-), U13.6
unnamed: R33.2, R35.2, U14.3 (+)
unnamed: R34.1, R36.1, U14.2 (-)

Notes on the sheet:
0v-3.3V Square wave
Buffer amplifier
Difference amplifier

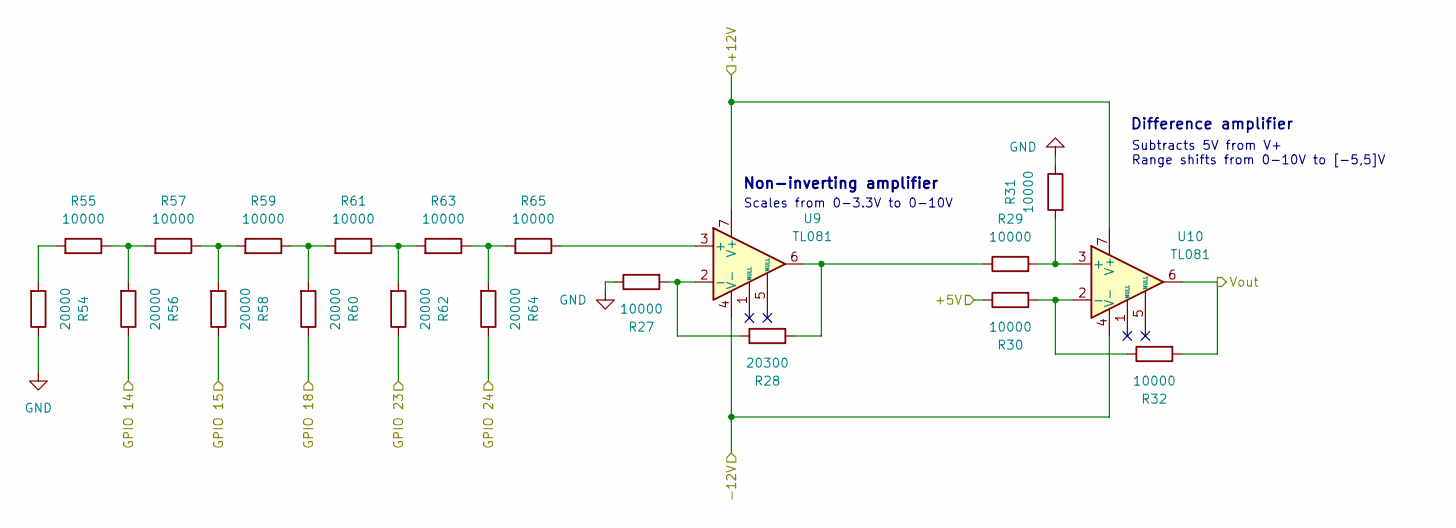
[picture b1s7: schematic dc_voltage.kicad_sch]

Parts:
R27, R29, R30, R31, R32, R55, R57, R59, R61, R63, R65: 10000; R_0603_1608Metric
R28: 20300; R_0603_1608Metric
R54, R56, R58, R60, R62, R64: 20000; R_0603_1608Metric
U9, U10: TL081; DIP-8_W7.62mm

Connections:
5V: R30.1; also elsewhere on the board
+12V: U9.7 (V+), U10.7 (V+); also elsewhere on the board
-12V: U9.4 (V-), U10.4 (V-); also elsewhere on the board
/GPIO14: R56.1; also elsewhere on the board
/GPIO15: R58.1; also elsewhere on the board
/GPIO18: R60.1; also elsewhere on the board
/GPIO23: R62.1; also elsewhere on the board
/GPIO24: R64.1; also elsewhere on the board
DC_REF_OUTPUT: R32.2, U10.6; also elsewhere on the board
GND: R27.1, R31.1, R54.1; also elsewhere on the board
unnamed: R28.2, R29.1, U9.6
unnamed: R54.2, R55.2
unnamed: R55.1, R56.2, R57.2
unnamed: R57.1, R58.2, R59.2
unnamed: R59.1, R60.2, R61.2
unnamed: R61.1, R62.2, R63.2
unnamed: R63.1, R64.2, R65.2
unnamed: R65.1, U9.3 (+)
unnamed: R27.2, R28.1, U9.2 (-)
unnamed: R29.2, R31.2, U10.3 (+)
unnamed: R30.2, R32.1, U10.2 (-)

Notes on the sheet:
Difference amplifier
Scales from 0-3.3V to 0-10V
Non-inverting amplifier
Subtracts 5V from V+ Range shifts from 0-10V to [-5,5]V

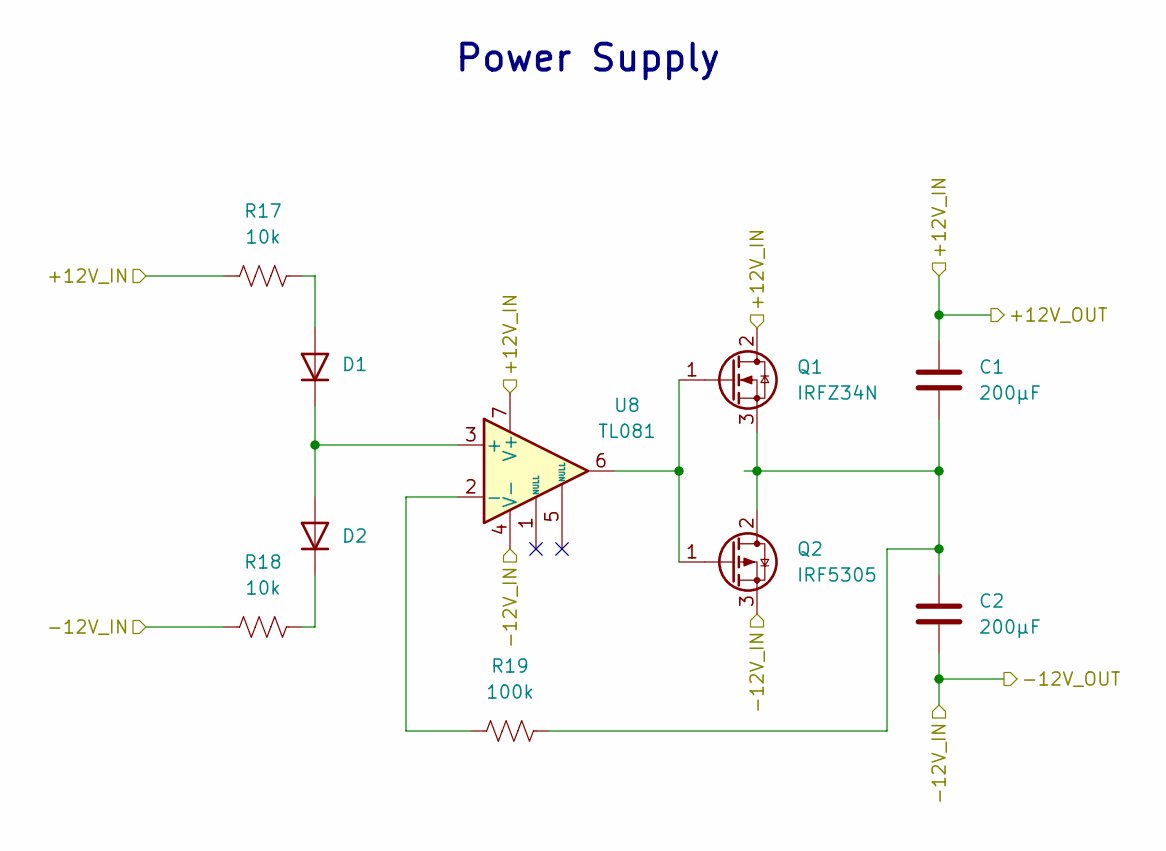
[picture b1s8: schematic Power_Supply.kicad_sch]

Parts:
C1, C2: 200µF; C_0603_1608Metric
D1, D2: 1N4148WT; D_SOD-523
Q1: IRFZ34N; TO-220-3_Vertical
Q2: IRF5305; TO-220-3_Vertical
R17, R18: 10k; R_0603_1608Metric
R19: 100k; R_0603_1608Metric
U8: TL081; DIP-8_W7.62mm_LongPads

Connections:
+12V: C1.1, Q1.2 (D), R17.2, U8.7 (V+); also elsewhere on the board
-12V: C2.2, Q2.3 (S), R18.2, U8.4 (V-); also elsewhere on the board
unnamed: D1.2 (A), R17.1
unnamed: D1.1 (K), D2.2 (A), U8.3 (+)
unnamed: D2.1 (K), R18.1
unnamed: Q1.1 (G), Q2.1 (G), U8.6
unnamed: C1.2, C2.1, Q1.3 (S), Q2.2 (D), R19.2
unnamed: R19.1, U8.2 (-)

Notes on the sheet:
Power Supply

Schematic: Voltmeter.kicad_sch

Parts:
R1, R2, R3, R5, R6: 10k; R_0603_1608Metric
R4: 30k; R_0603_1608Metric
U1: LM339; DIP-14_W7.62mm
U2: MCP4131; DIP-8_W7.62mm
U3, U4: TL081; DIP-8_W7.62mm

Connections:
3.3V: R6.2, U2.5 (P0A), U2.8 (V_{DD}); also elsewhere on the board
5V: R2.1; also elsewhere on the board
+12V: U3.7 (V+), U4.7 (V+); also elsewhere on the board
-12V: U3.4 (V-), U4.4 (V-); also elsewhere on the board
/GPIO8: U2.1 (~CS); also elsewhere on the board
/GPIO10: U2.3 (SDI/SDO); also elsewhere on the board
/GPIO11: U2.2 (SCK); also elsewhere on the board
/GPIO20: R6.1, U1.2; also elsewhere on the board
/Voltmeter/VOLTAGE_INPUT: R1.1; also elsewhere on the board
GND: U2.4 (V_{SS}), U2.7 (P0B), U3.3 (+), U4.3 (+); also elsewhere on the board
unnamed: R3.2, R4.1, U3.6
unnamed: R5.2, U1.5 (+), U4.6
unnamed: U1.4 (-), U2.6 (P0W)
unnamed: R1.2, R2.2, R3.1, U3.2 (-)
unnamed: R4.2, R5.1, U4.2 (-)

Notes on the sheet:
Voltmeter

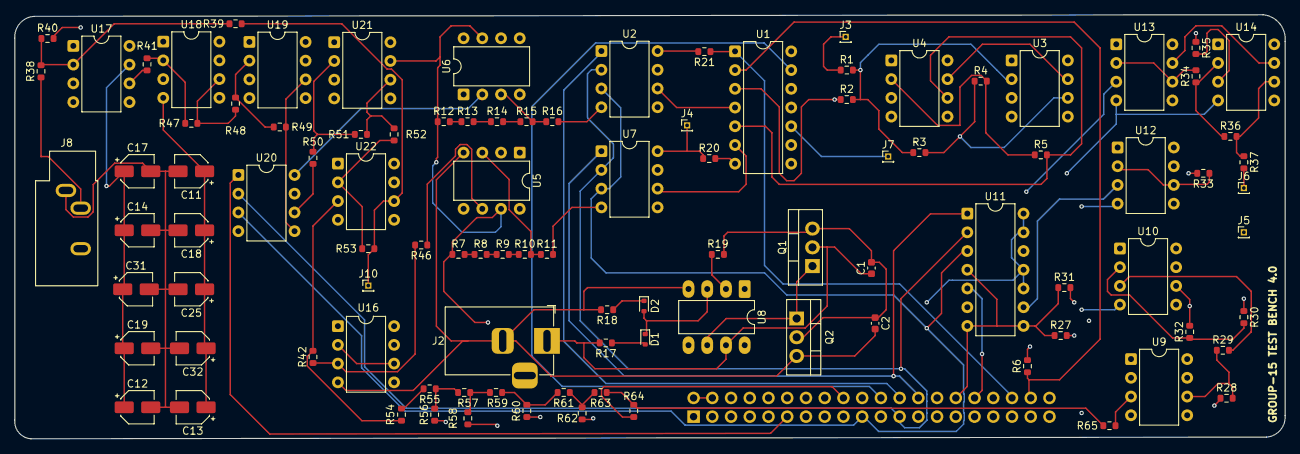
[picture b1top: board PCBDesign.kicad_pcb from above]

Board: 4 copper layers, 172.3 x 57.5 mm, 103 parts (1 on the bottom side), 75 nets.
